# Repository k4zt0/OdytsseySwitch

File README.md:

# Odytssey Switch

Five-key wireless macropad built around an ESP32-S3, with a 0.96" OLED and a
thumbstick. Reaches a host over USB HID, BLE HID, or Wi-Fi, and can drive other
gear through its I2C, UART and addressable-LED outputs.

## Hardware

| Block   | Part |
| ------- | ---- |
| MCU     | ESP32-S3-WROOM-1 — BLE 5, Wi-Fi 4, native USB, pre-certified module |
| Keys    | 5 x Kailh MX hotswap sockets on GPIO 4, 5, 6, 7, 15 |
| Stick   | 2-axis thumbstick, X on IO1 and Y on IO2 (ADC1 only), press on IO16 |
| Display | SSD1306 0.96" 128x64 over I2C0 (SDA IO8, SCL IO9) |
| Outputs | Qwiic I2C port, WS2812 strip header, UART0 + 4 spare GPIO |
| Power   | USB-C bus powered, AP2112K-3.3 LDO, USBLC6-2SC6 ESD array |

Both analogue axes sit on ADC1 because ADC2 stops working once the radio is
transmitting. The thumbstick is fed 3V3 rather than 5V so its wiper range
matches the ADC full scale.

## Board

- 112 x 102 mm, 2 layer FR-4, 1.6 mm, 3 mm corner radius
- Front carries the keys and the two module sockets; every other part is on the
  back, so the panel reflows from one side only
- No through-hole parts — the module connectors are SMD sockets, so assembly
  needs no soldering at all
- Routed on both layers, 345 tracks and 207 vias, ground pours stitched
  together and bonded solid to pads rather than through thermal spokes
- The ESP32 module's antenna overhangs the left edge; keep metal away from it
- Ground pours on both layers, stitched with vias

## Assembly

Order with SMT assembly. Nothing needs soldering afterwards:

1. Plug the OLED module into J2
2. Plug the thumbstick module into J7
3. Drop five MX switches into the hotswap sockets
4. Fit keycaps

Buy modules that already have their pin headers soldered on.

## Fabrication

`fab/` holds Gerbers, Excellon drill files, the drill map, the `.gbrjob`,
pick-and-place data and the BOM.

| Setting | Value |
| ------- | ----- |
| Base material | FR-4, TG130-140 |
| Layers | 2 |
| Thickness | 1.6 mm |
| Panel | single PCB |
| Surface finish | ENIG |
| Min hole | 0.2 mm |

The 1.6 mm thickness is not optional: MX hotswap sockets are cut for it.

## Layout

Third-party footprints come from [kiswitch](https://github.com/kiswitch/kiswitch);
only `Switch_Keyboard_Hotswap_Kailh.pretty` is vendored here, under `libs/`.
`fp-lib-table` points at it with `${KIPRJMOD}`.

## Status

Complete and ready to order.

| Check | Result |
| ----- | ------ |
| ERC | 0 errors |
| DRC | 0 errors |
| Unconnected | 0 |
| Schematic parity | 0 issues |
| Netlist vs. design intent | checked pin by pin, no mismatch |

Two DRC warnings remain and are both expected: the ESP32 module's silkscreen
crosses the left board edge by 0.15 mm, which is the deliberate antenna
overhang, and sixteen footprints differ from their library copies, which has no
bearing on fabrication.

The autorouter did not length-match the USB differential pair. At USB 2.0 Full
Speed that is not a problem in practice, but tidy those two traces by hand if
you want it right.

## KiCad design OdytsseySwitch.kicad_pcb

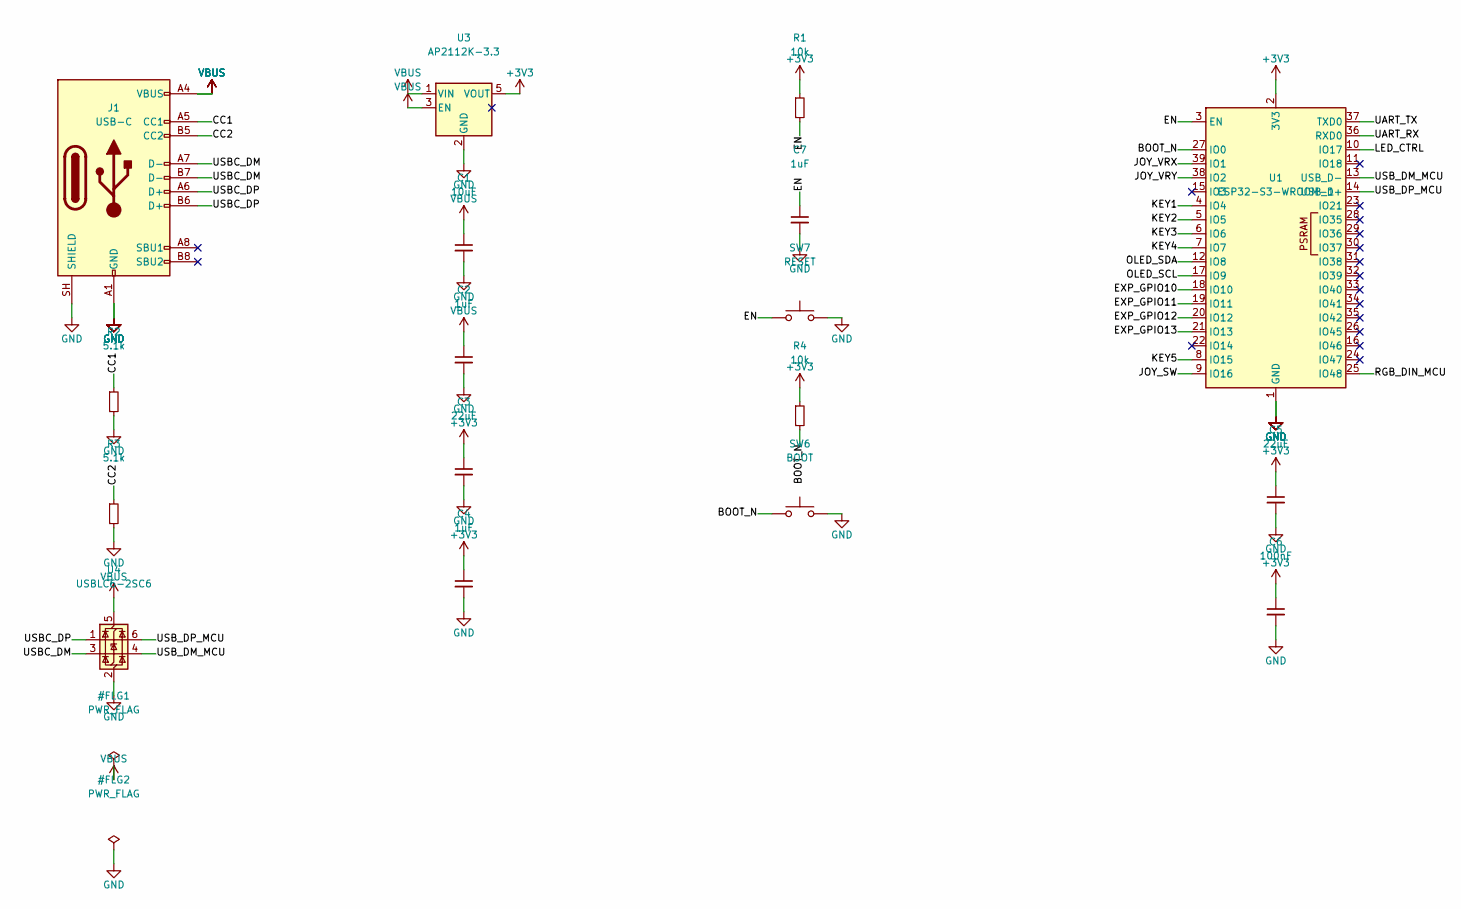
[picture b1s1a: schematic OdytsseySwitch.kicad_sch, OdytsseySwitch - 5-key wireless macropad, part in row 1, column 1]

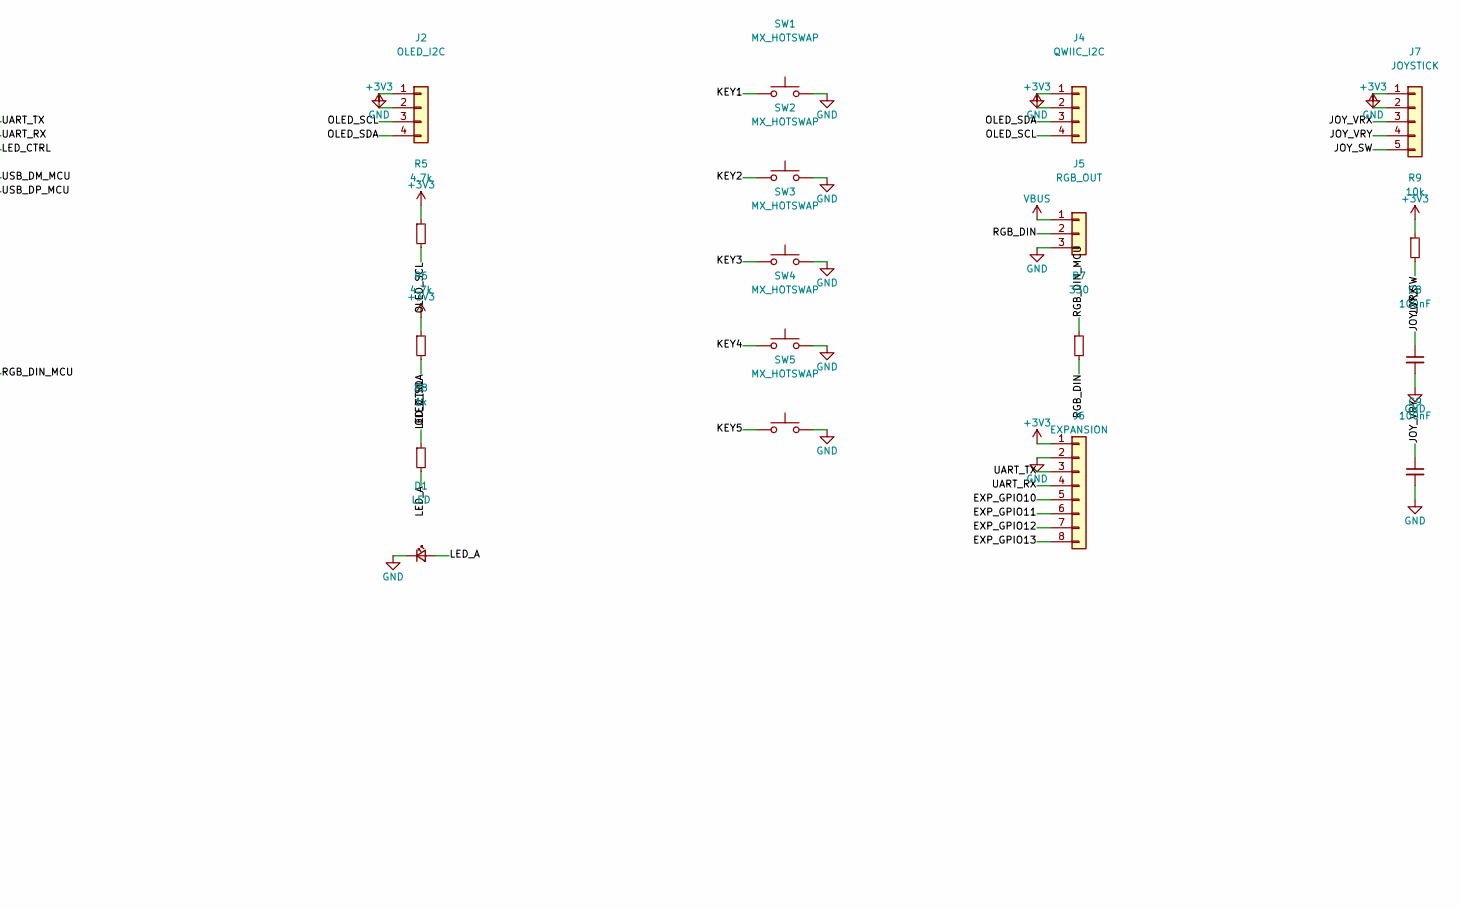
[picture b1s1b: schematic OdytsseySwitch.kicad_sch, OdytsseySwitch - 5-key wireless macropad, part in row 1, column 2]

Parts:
C1: 10uF; C_1206_3216Metric
C2, C4, C7: 1uF; C_0603_1608Metric
C3, C5: 22uF; C_1206_3216Metric
C6, C8, C9: 100nF; C_0603_1608Metric
D1: LED; LED_0603_1608Metric
J1: USB-C; USB_C_Receptacle_HRO_TYPE-C-31-M-12
J2: OLED_I2C; PinSocket_1x04_P2.54mm_Vertical_SMD_Pin1Left
J4: QWIIC_I2C; JST_SH_SM04B-SRSS-TB_1x04-1MP_P1.00mm_Horizontal
J5: RGB_OUT; PinSocket_1x03_P2.54mm_Vertical_SMD_Pin1Left
J6: EXPANSION; PinSocket_1x08_P2.54mm_Vertical_SMD_Pin1Left
J7: JOYSTICK; PinSocket_1x05_P2.54mm_Vertical_SMD_Pin1Left
R1, R4, R9: 10k; R_0603_1608Metric
R2, R3: 5.1k; R_0603_1608Metric
R5, R6: 4.7k; R_0603_1608Metric
R7: 330; R_0603_1608Metric
R8: 1k; R_0603_1608Metric
SW1, SW2, SW3, SW4, SW5: MX_HOTSWAP; SW_Hotswap_Kailh_MX_1.00u
SW6: BOOT; SW_SPST_TL3342
SW7: RESET; SW_SPST_TL3342
U1: ESP32-S3-WROOM-1
U3: AP2112K-3.3; SOT-23-5
U4: USBLC6-2SC6; SOT-23-6

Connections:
+3V3: C3.1, C4.1, C5.1, C6.1, J2.2, J4.2, J6.1, J7.2, R1.1, R4.1, R5.1, R6.1, R9.1, U1.2 (3V3), U3.5 (VOUT)
/BOOT_N: R4.2, SW6.1, U1.27 (IO0)
/CC1: J1.A5 (CC1), R2.1
/CC2: J1.B5 (CC2), R3.1
/EN: C7.1, R1.2, SW7.1, U1.3 (EN)
/EXP_GPIO10: J6.5, U1.18 (IO10)
/EXP_GPIO11: J6.6, U1.19 (IO11)
/EXP_GPIO12: J6.7, U1.20 (IO12)
/EXP_GPIO13: J6.8, U1.21 (IO13)
/JOY_SW: J7.5, R9.2, U1.9 (IO16)
/JOY_VRX: C8.1, J7.3, U1.39 (IO1)
/JOY_VRY: C9.1, J7.4, U1.38 (IO2)
/KEY1: SW1.1, U1.4 (IO4)
/KEY2: SW2.1, U1.5 (IO5)
/KEY3: SW3.1, U1.6 (IO6)
/KEY4: SW4.1, U1.7 (IO7)
/KEY5: SW5.1, U1.8 (IO15)
/LED_A: D1.2 (A), R8.2
/LED_CTRL: R8.1, U1.10 (IO17)
/OLED_SCL: J2.3, J4.4, R5.2, U1.17 (IO9)
/OLED_SDA: J2.4, J4.3, R6.2, U1.12 (IO8)
/RGB_DIN: J5.2, R7.2
/RGB_DIN_MCU: R7.1, U1.25 (IO48)
/UART_RX: J6.4, U1.36 (RXD0)
/UART_TX: J6.3, U1.37 (TXD0)
/USBC_DM: J1.A7 (D-), J1.B7 (D-), U4.3 (I/O2)
/USBC_DP: J1.A6 (D+), J1.B6 (D+), U4.1 (I/O1)
/USB_DM_MCU: U1.13 (USB_D-), U4.4 (I/O2)
/USB_DP_MCU: U1.14 (USB_D+), U4.6 (I/O1)
GND: C1.2, C2.2, C3.2, C4.2, C5.2, C6.2, C7.2, C8.2, C9.2, D1.1 (K), J1.A1 (GND), J1.A12 (GND), J1.B1 (GND), J1.B12 (GND), J1.SH (SHIELD), J2.1, J4.1, J5.3, J6.2, J7.1, R2.2, R3.2, SW1.2, SW2.2, SW3.2, SW4.2, SW5.2, SW6.2, SW7.2, U1.1 (GND), U1.40 (GND), U1.41 (GND), U3.2 (GND), U4.2 (GND)
VBUS: C1.1, C2.1, J1.A4 (VBUS), J1.A9 (VBUS), J1.B4 (VBUS), J1.B9 (VBUS), J5.1, U3.1 (VIN), U3.3 (EN), U4.5 (VBUS)

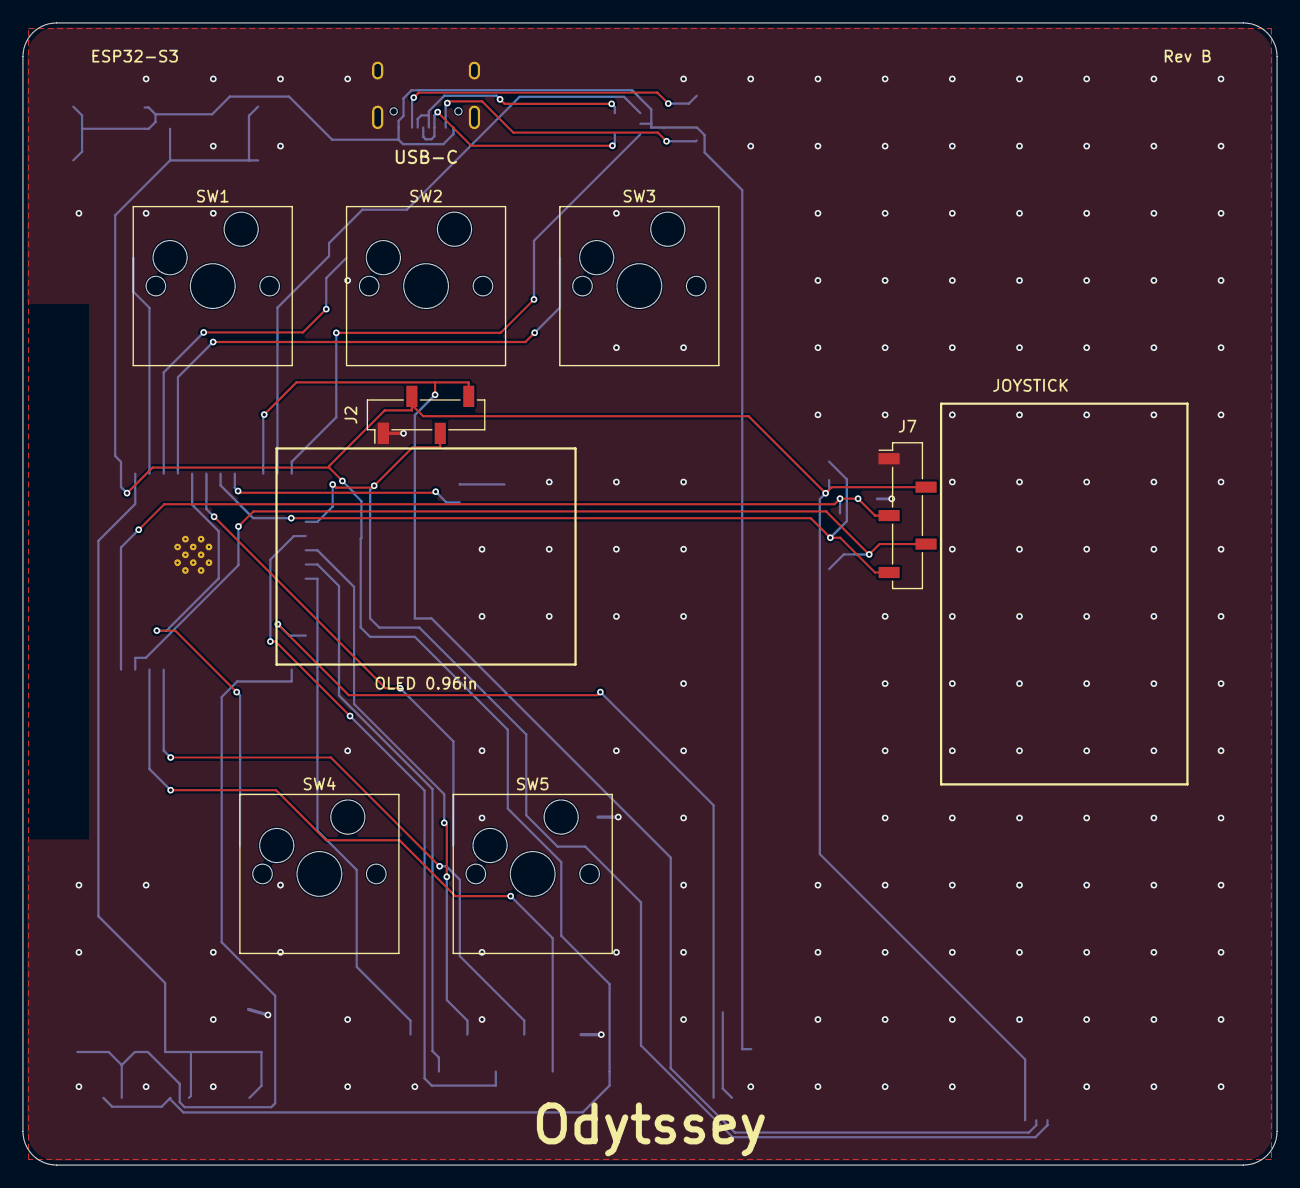
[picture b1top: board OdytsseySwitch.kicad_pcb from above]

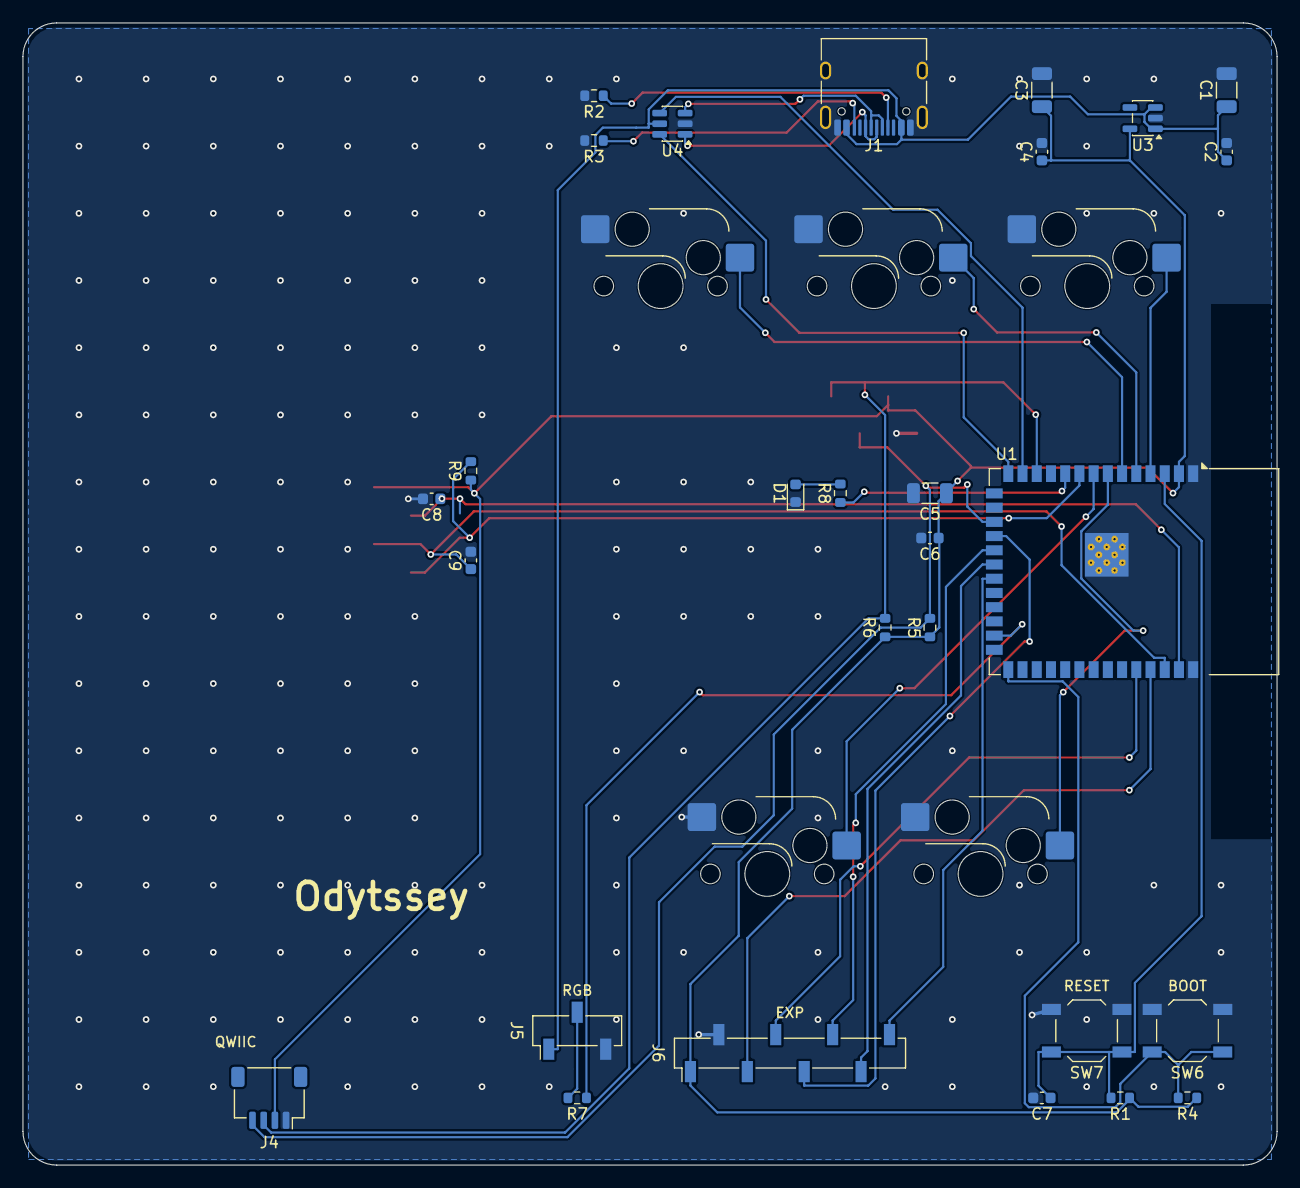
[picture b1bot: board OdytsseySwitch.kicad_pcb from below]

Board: 2 copper layers, 112.0 x 102.0 mm, 35 parts (28 on the bottom side), 31 nets.

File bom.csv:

"Reference","Value","Footprint","Description","QUANTITY"
"C1","10uF","Capacitor_SMD:C_1206_3216Metric","LDO input bulk","1"
"C2,C4,C7","1uF","Capacitor_SMD:C_0603_1608Metric","EN power-on reset delay,LDO input,LDO output","3"
"C3,C5","22uF","Capacitor_SMD:C_1206_3216Metric","LDO output bulk,Module supply bulk - covers WiFi TX peaks","2"
"C6","100nF","Capacitor_SMD:C_0603_1608Metric","Decoupling - module 3V3 pin","1"
"D1","LED","LED_SMD:LED_0603_1608Metric","Status LED","1"
"J1","USB-C","Connector_USB:USB_C_Receptacle_HRO_TYPE-C-31-M-12","USB 2.0 Type-C receptacle, 16 pin","1"
"J2","OLED_I2C","Connector_PinHeader_2.54mm:PinHeader_1x04_P2.54mm_Vertical","SSD1306 0.96in 128x64 OLED module (GND/VCC/SCL/SDA)","1"
"J4","QWIIC_I2C","Connector_JST:JST_SH_SM04B-SRSS-TB_1x04-1MP_P1.00mm_Horizontal","Qwiic/STEMMA QT I2C output port (GND/3V3/SDA/SCL)","1"
"J5","RGB_OUT","Connector_PinHeader_2.54mm:PinHeader_1x03_P2.54mm_Vertical","Addressable LED strip output (5V/DIN/GND)","1"
"J6","EXPANSION","Connector_PinHeader_2.54mm:PinHeader_1x08_P2.54mm_Vertical","Expansion header - UART0 TX/RX and 4 spare GPIO","1"
"R1,R4","10k","Resistor_SMD:R_0603_1608Metric","EN pull-up,IO0 strapping pull-up","2"
"R2,R3","5.1k","Resistor_SMD:R_0603_1608Metric","Type-C CC pull-down (UFP)","2"
"R5,R6","4.7k","Resistor_SMD:R_0603_1608Metric","I2C pull-up","2"
"R7","330","Resistor_SMD:R_0603_1608Metric","RGB data-line series damping","1"
"R8","1k","Resistor_SMD:R_0603_1608Metric","Status LED current limit","1"
"SW1-SW5","MX_HOTSWAP","Switch_Keyboard_Hotswap_Kailh:SW_Hotswap_Kailh_MX_1.00u","Kailh MX hotswap socket, key 1,Kailh MX hotswap socket, key 2,Kailh MX hotswap socket, key 3,Kailh MX hotswap socket, key 4,Kailh MX hotswap socket, key 5","5"
"SW6","BOOT","Button_Switch_SMD:SW_SPST_TL3342","BOOT - hold at reset for USB download mode","1"
"SW7","RESET","Button_Switch_SMD:SW_SPST_TL3342","Reset button","1"
"U1","ESP32-S3-WROOM-1","RF_Module:ESP32-S3-WROOM-1","Xtensa LX7 dual core - BLE 5, WiFi 4, native USB (pre-certified module)","1"
"U3","AP2112K-3.3","Package_TO_SOT_SMD:SOT-23-5","600 mA 3.3 V LDO","1"
"U4","USBLC6-2SC6","Package_TO_SOT_SMD:SOT-23-6","USB data-line ESD protection array","1"
